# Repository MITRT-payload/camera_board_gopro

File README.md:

# camera_board_gopro
Requested by Elena R,

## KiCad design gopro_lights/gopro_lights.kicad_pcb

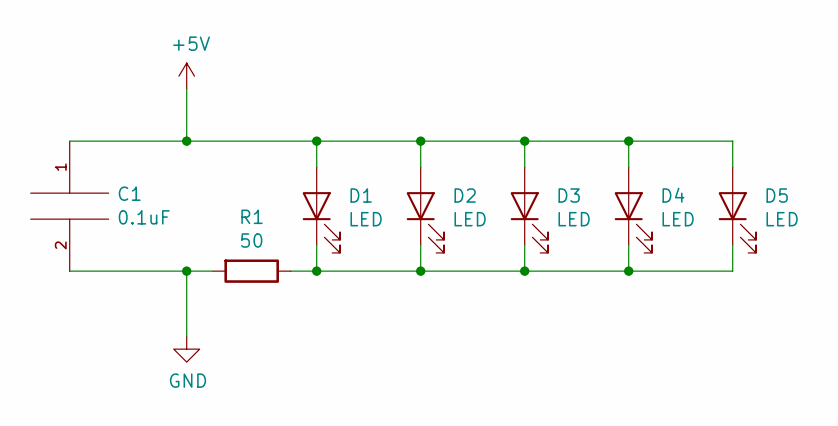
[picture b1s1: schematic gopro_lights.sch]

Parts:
C1: 0.1uF
D1, D2, D3, D4, D5: LED
R1: 50

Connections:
+5V: C1.1, D1.2 (A), D2.2 (A), D3.2 (A), D4.2 (A), D5.2 (A); also elsewhere on the board
GND: C1.2, R1.2
unnamed 2: D1.1 (K), D2.1 (K), D3.1 (K), D4.1 (K), D5.1 (K), R1.1; also elsewhere on the board

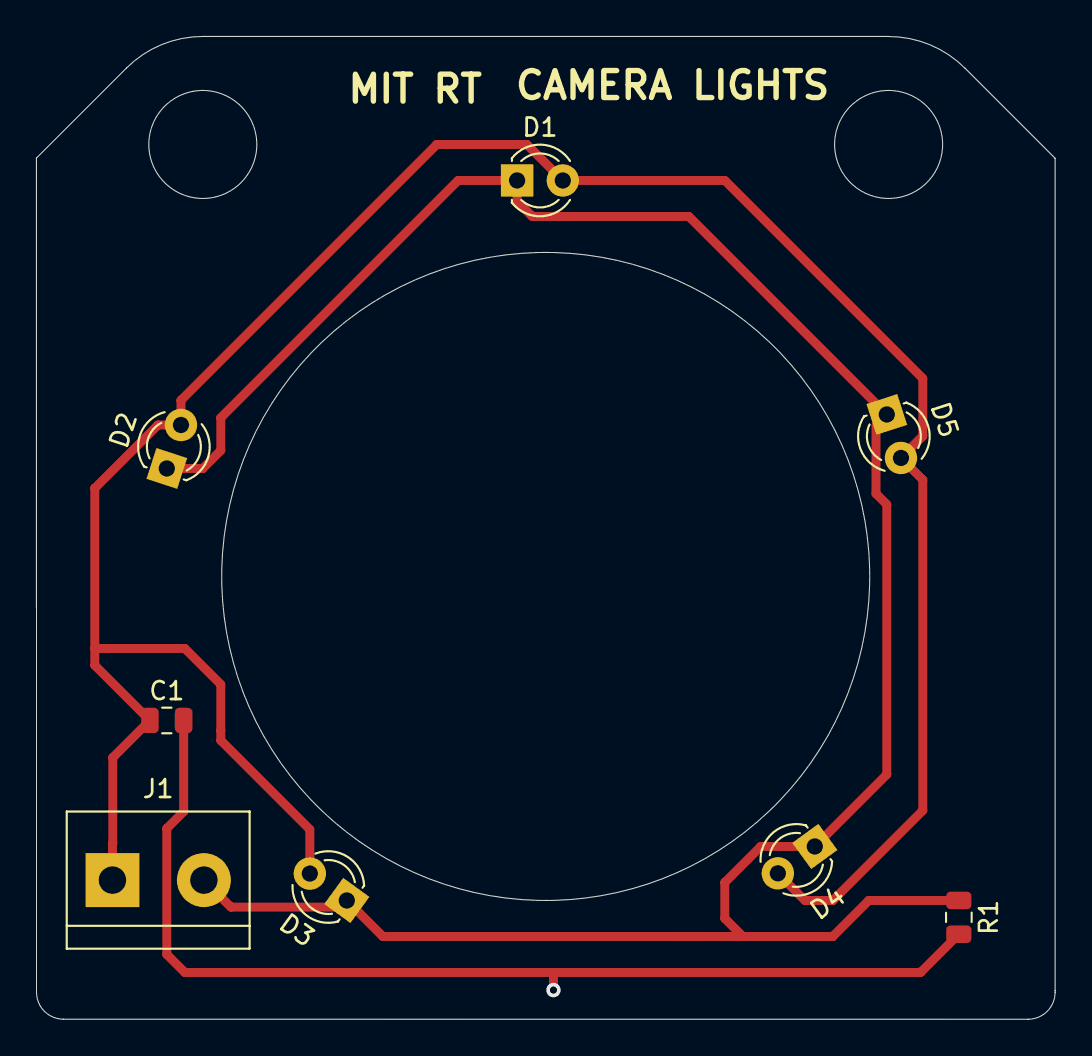
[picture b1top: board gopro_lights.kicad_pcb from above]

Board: 2 copper layers, 56.6 x 54.6 mm, 8 parts (0 on the bottom side), 3 nets.

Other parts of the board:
J1: Screw_Terminal_01x02; TerminalBlock_bornier-2_P5.08mm

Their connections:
+5V: J1.1; also elsewhere on the board
unnamed 2: J1.2; also elsewhere on the board

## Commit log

2019-11-19 feat: go pro camera v1
2019-11-19 fix: for hole size
2019-11-20 chore: adding files and .step
2019-11-22 feat: board files
